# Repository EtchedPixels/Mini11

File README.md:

# Mini11: A Small 68HC11A System

The Mini11 is a small board that is designed to provide a complete large
68HC11 environment with a fairly low chip count. It provides 16K of ROM and
512K of RAM as well as breaking out all the spare I/O including the serial
and SPI in useful ways.

To keep cost down it's designed to use the many old 68HC11A series parts
that can be found in junk boxes and old boards. This has a different pinout
to the later processor variants.

## Requirements

- 68HC11A series processor (A0/A1/A8). 68HC811A probably works too
- 512K SRAM
- 27C256 or 28C256
- 74HC(T)139
- 74HC(T)00
- 74HC(T)573
- DS1233 reset controller
- 8MHz crystal
- pinheaders, sockets, resistors etc

## Construction

As the 68HC11 can be serial bootstrapped it is possible to assemble the
board and fit all the discrete parts and only the 68HC11 into its socket.
Fit jumpers JP1 and JP2 and apply power. You should be able to talk to the
board with db11 or similar tools.

If you have a part with ROM then you should also be able to boot from the
ROM if you boot with JP1 and JP2 removed. If the ROM contains Buffalo as
is usual then you will also need to jumper PE0 to ground. A 68HC11A8 with
Buffalo should then produce a boot message and you'll be able to talk to
the monitor.

The boot mode can also be used to check out the board after the other parts
are fitted. You can boot in single chip mode and then use db11 to turn off the
single chip mode and then check that the memory is behaving. Port A controls
the memory banking. Bit 3 turns the ROM on and off, bits 4-6 are the memory
bank.

With all the parts fitted you can burn firmware of choice into the ROM and
with the jumpers removed the chip should boot the firmware. Remember to use
the ".burn" file with the provided firmware or the tools to flip bit 0 and 2
as the board has D0 and D2 switched on the ROM

The provided firmware simply intializes the SD interface, loads the
first sector and runs it.

### Note

You cannot run an unmodified Buffalo from the ROM. It uses Port A pins for
tracing and this conflicts with the memory banking.

## ROM options

For a 27C256 you can load different firmware into each 16K bank and select
using JP3. For a 28C256 burn the firmware into the upper 16K and jumper JP3
to VCC.

## Rescuing Recalcitrant 68HC11A Parts

If you have problems with the 68HC11A such as it only coming up in bootstrap
mode then there are a few things to check.

### Wrong Config Byte

If the CONFIG byte is set to map in the internal ROM and the ROM contains
garbage or is absent (eg on a 68HC11A0/A1 part) then you can boot it into
single chip mode and use db11 to change the config byte to 0x0C or similar.

### Protected EEROM

The internal EEROM has protection options and some devices wih custom
firmware will set them. These can still be used as they will erase the
EEPROM when the serial boot is triggered. This will put 0F into the CONFIG
register so that will also then need reprogramming.

### Did You Remember D0/D2 Are Swapped In Your ROM Image

No.. opps

## External Interfaces

### J2: Serial (TTL Level)

Simple three wire interface with no flow control. Usually run at 9600 baud.

### J3: SPI (5v)

SPI. Provides the expected SPI interfaces as well as two chip select lines,
reset and the external IRQ (pulled up). Intended for an SD card and
optionally additional devices with an SPI mux/demux board. Remember to use
an SD adapter with voltage shifting.

### J4: Power

5v and ground, needs to be properly regulated. The board has an onboard
reset generator to handle power coming up gracefully.

## J5: GPIO

Three input ports mapped to port A bits 0-2

### J6: Analogue

Port E of the 68HC11.

## Jumpers

### JP1: MODA

Fit the jumper to set MODA low

### JP2: MODB

Fit the jumper to set MODB low

### JP3: ROM Select

Select bank on 27C256, set to 5V with a 28C256

## Software

At this point FUZIX. Build the "mini11" target, write the generated SD card
image raw to an SD card and boot the mini11 with it inserted. The console
runs at 9600 baud.

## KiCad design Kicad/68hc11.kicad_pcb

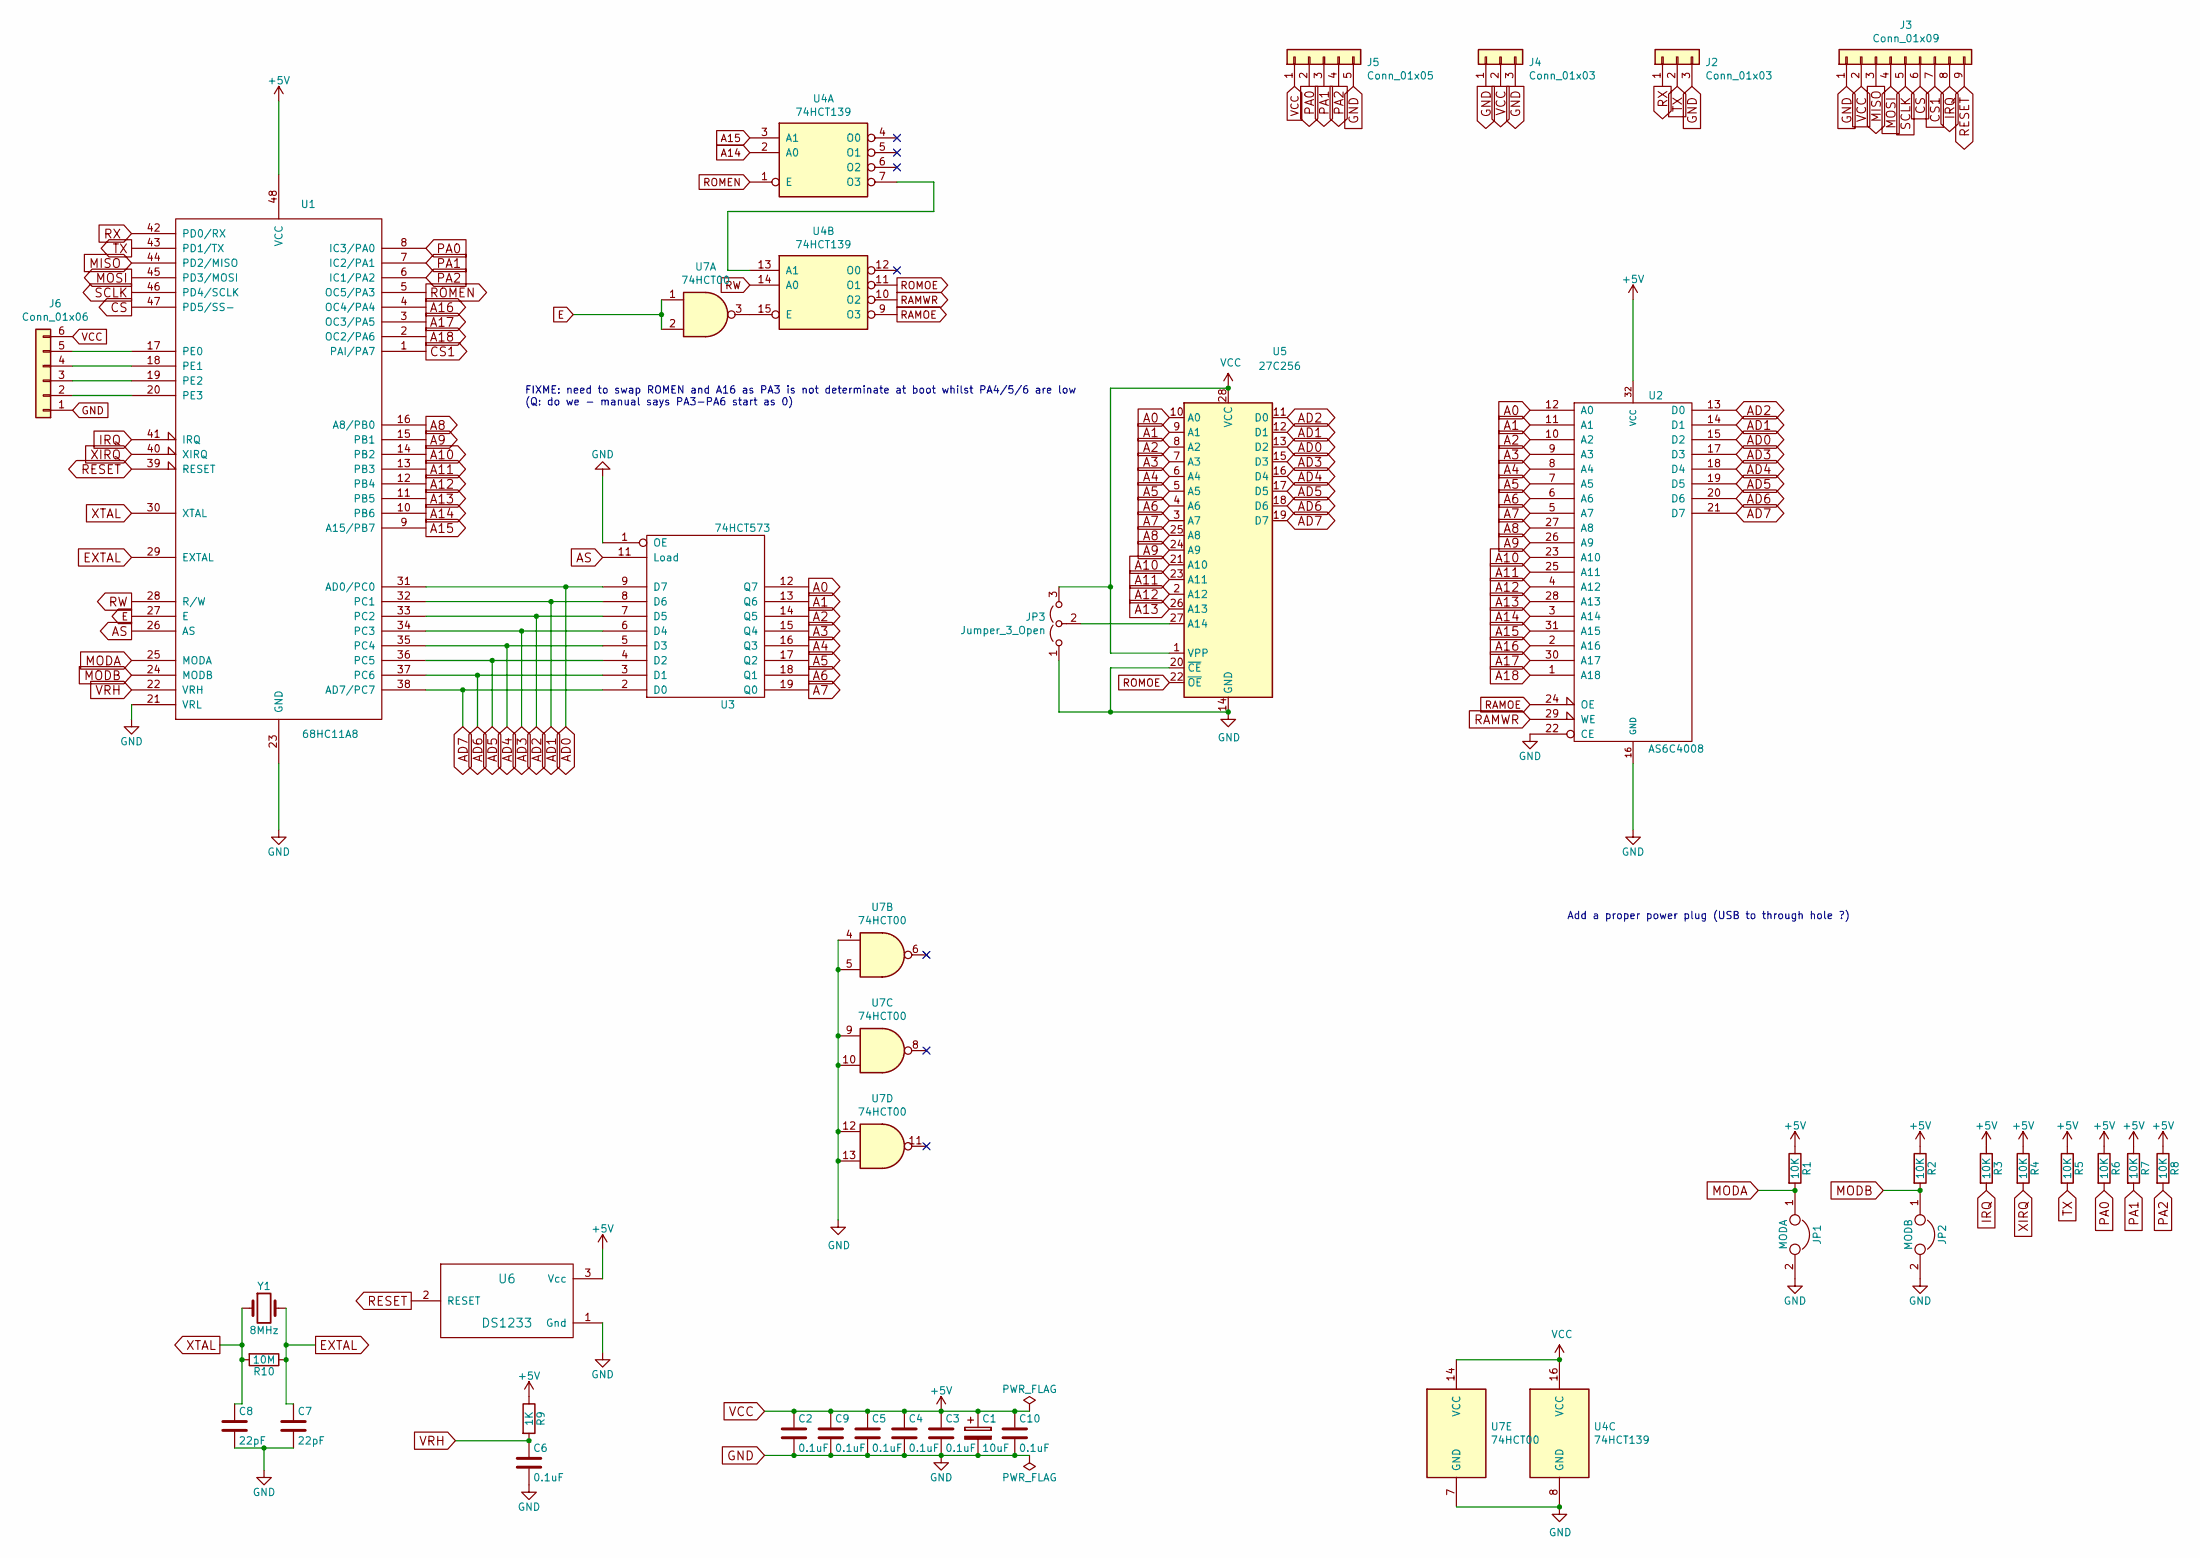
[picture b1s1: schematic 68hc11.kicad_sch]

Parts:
C1: 10uF; CP_Radial_D5.0mm_P2.00mm
C2, C3, C4, C5, C6, C10: 0.1uF; C_Disc_D3.0mm_W1.6mm_P2.50mm
C7, C8: 22pF; C_Disc_D3.0mm_W1.6mm_P2.50mm
C9: 0.1uF; C_Disc_D3.0mm_W2.0mm_P2.50mm
J2: Conn_01x03; PinHeader_1x03_P2.54mm_Horizontal
J3: Conn_01x09; PinHeader_1x09_P2.54mm_Vertical
J4: Conn_01x03; PinHeader_1x03_P2.54mm_Vertical
J5: Conn_01x05; PinHeader_1x05_P2.54mm_Vertical
J6: Conn_01x06; PinHeader_1x06_P2.54mm_Horizontal
JP1: MODA; PinHeader_1x02_P2.54mm_Vertical
JP2: MODB; PinHeader_1x02_P2.54mm_Vertical
JP3: Jumper_3_Open; PinHeader_1x03_P2.54mm_Vertical
R1, R2, R3, R4, R5, R6, R7, R8: 10K; R_Axial_DIN0207_L6.3mm_D2.5mm_P10.16mm_Horizontal
R9: 1K; R_Axial_DIN0207_L6.3mm_D2.5mm_P10.16mm_Horizontal
R10: 10M; R_Axial_DIN0207_L6.3mm_D2.5mm_P10.16mm_Horizontal
U1: 68HC11A8; DIP-48_W15.24mm
U2: AS6C4008; DIP-32_W15.24mm
U3: 74HCT573; DIP-20_W7.62mm
U4: 74HCT139; DIP-16_W7.62mm
U5: 27C256; DIP-28_W15.24mm
U6: DS1233; TO-92_Inline_Narrow_Oval
U7: 74HCT00; DIP-14_W7.62mm
Y1: 8MHz; Crystal_HC49-U_Vertical

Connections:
A0: U2.12 (A0), U3.12 (Q7), U5.10 (A0)
A1: U2.11 (A1), U3.13 (Q6), U5.9 (A1)
A2: U2.10 (A2), U3.14 (Q5), U5.8 (A2)
A3: U2.9 (A3), U3.15 (Q4), U5.7 (A3)
A4: U2.8 (A4), U3.16 (Q3), U5.6 (A4)
A5: U2.7 (A5), U3.17 (Q2), U5.5 (A5)
A6: U2.6 (A6), U3.18 (Q1), U5.4 (A6)
A7: U2.5 (A7), U3.19 (Q0), U5.3 (A7)
A8: U1.16 (A8/PB0), U2.27 (A8), U5.25 (A8)
A9: U1.15 (PB1), U2.26 (A9), U5.24 (A9)
A10: U1.14 (PB2), U2.23 (A10), U5.21 (A10)
A11: U1.13 (PB3), U2.25 (A11), U5.23 (A11)
A12: U1.12 (PB4), U2.4 (A12), U5.2 (A12)
A13: U1.11 (PB5), U2.28 (A13), U5.26 (A13)
A14: U1.10 (PB6), U2.3 (A14), U4.2 (A0)
A15: U1.9 (A15/PB7), U2.31 (A15), U4.3 (A1)
A16: U1.4 (OC4/PA4), U2.2 (A16)
A17: U1.3 (OC3/PA5), U2.30 (A17)
A18: U1.2 (OC2/PA6), U2.1 (A18)
AD0: U1.31 (AD0/PC0), U2.15 (D2), U3.9 (D7), U5.13 (D2)
AD1: U1.32 (PC1), U2.14 (D1), U3.8 (D6), U5.12 (D1)
AD2: U1.33 (PC2), U2.13 (D0), U3.7 (D5), U5.11 (D0)
AD3: U1.34 (PC3), U2.17 (D3), U3.6 (D4), U5.15 (D3)
AD4: U1.35 (PC4), U2.18 (D4), U3.5 (D3), U5.16 (D4)
AD5: U1.36 (PC5), U2.19 (D5), U3.4 (D2), U5.17 (D5)
AD6: U1.37 (PC6), U2.20 (D6), U3.3 (D1), U5.18 (D6)
AD7: U1.38 (AD7/PC7), U2.21 (D7), U3.2 (D0), U5.19 (D7)
AS: U1.26 (AS), U3.11 (Load)
CS: J3.6, U1.47 (PD5/SS-)
CS1: J3.7, U1.1 (PAI/PA7)
E: U1.27 (E), U7.1, U7.2
EXTAL: C7.1, R10.1, U1.29 (EXTAL), Y1.2
GND: C1.2, C2.2, C3.2, C4.2, C5.2, C6.2, C7.2, C8.2, C9.2, C10.2, J2.3, J3.1, J4.1, J4.3, J5.5, J6.1, JP1.2, JP2.2, JP3.1 (A), U1.21 (VRL), U1.23 (GND), U2.16 (GND), U2.22 (CE), U3.1 (OE), U3.10 (GND), U4.8 (GND), U5.14 (GND), U5.20 (~CE), U6.1 (Gnd), U7.4, U7.5, U7.7 (GND), U7.9, U7.10, U7.12, U7.13
IRQ: J3.8, R3.2, U1.41 (IRQ)
MISO: J3.3, U1.44 (PD2/MISO)
MODA: JP1.1, R1.2, U1.25 (MODA)
MODB: JP2.1, R2.2, U1.24 (MODB)
MOSI: J3.4, U1.45 (PD3/MOSI)
unnamed: J6.2, U1.20 (PE3)
unnamed: J6.3, U1.19 (PE2)
unnamed: J6.4, U1.18 (PE1)
unnamed: J6.5, U1.17 (PE0)
unnamed: JP3.2 (C), U5.27 (A14)
unnamed: U4.7 (O3), U4.13 (A1)
unnamed: U4.15 (E), U7.3
PA0: J5.2, R6.2, U1.8 (IC3/PA0)
PA1: J5.3, R7.2, U1.7 (IC2/PA1)
PA2: J5.4, R8.2, U1.6 (IC1/PA2)
RAMOE: U2.24 (OE), U4.9 (O3)
RAMWR: U2.29 (WE), U4.10 (O2)
RESET: J3.9, U1.39 (RESET), U6.2 (RESET)
ROMEN: U1.5 (OC5/PA3), U4.1 (E)
ROMOE: U4.11 (O1), U5.22 (~OE)
RW: U1.28 (R/W), U4.14 (A0)
RX: J2.1, U1.42 (PD0/RX)
SCLK: J3.5, U1.46 (PD4/SCLK)
TX: J2.2, R5.2, U1.43 (PD1/TX)
VCC: C1.1, C2.1, C3.1, C4.1, C5.1, C9.1, C10.1, J3.2, J4.2, J5.1, J6.6, JP3.3 (B), R1.1, R2.1, R3.1, R4.1, R5.1, R6.1, R7.1, R8.1, R9.1, U1.48 (VCC), U2.32 (VCC), U3.20 (VCC), U4.16 (VCC), U5.1 (VPP), U5.28 (VCC), U6.3 (Vcc), U7.14 (VCC)
VRH: C6.1, R9.2, U1.22 (VRH)
XIRQ: R4.2, U1.40 (XIRQ)
XTAL: C8.1, R10.2, U1.30 (XTAL), Y1.1

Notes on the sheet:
FIXME: need to swap ROMEN and A16 as PA3 is not determinate at boot whilst PA4/5/6 are low (Q: do we - manual says PA3-PA6 start as 0)
Add a proper power plug (USB to through hole ?)

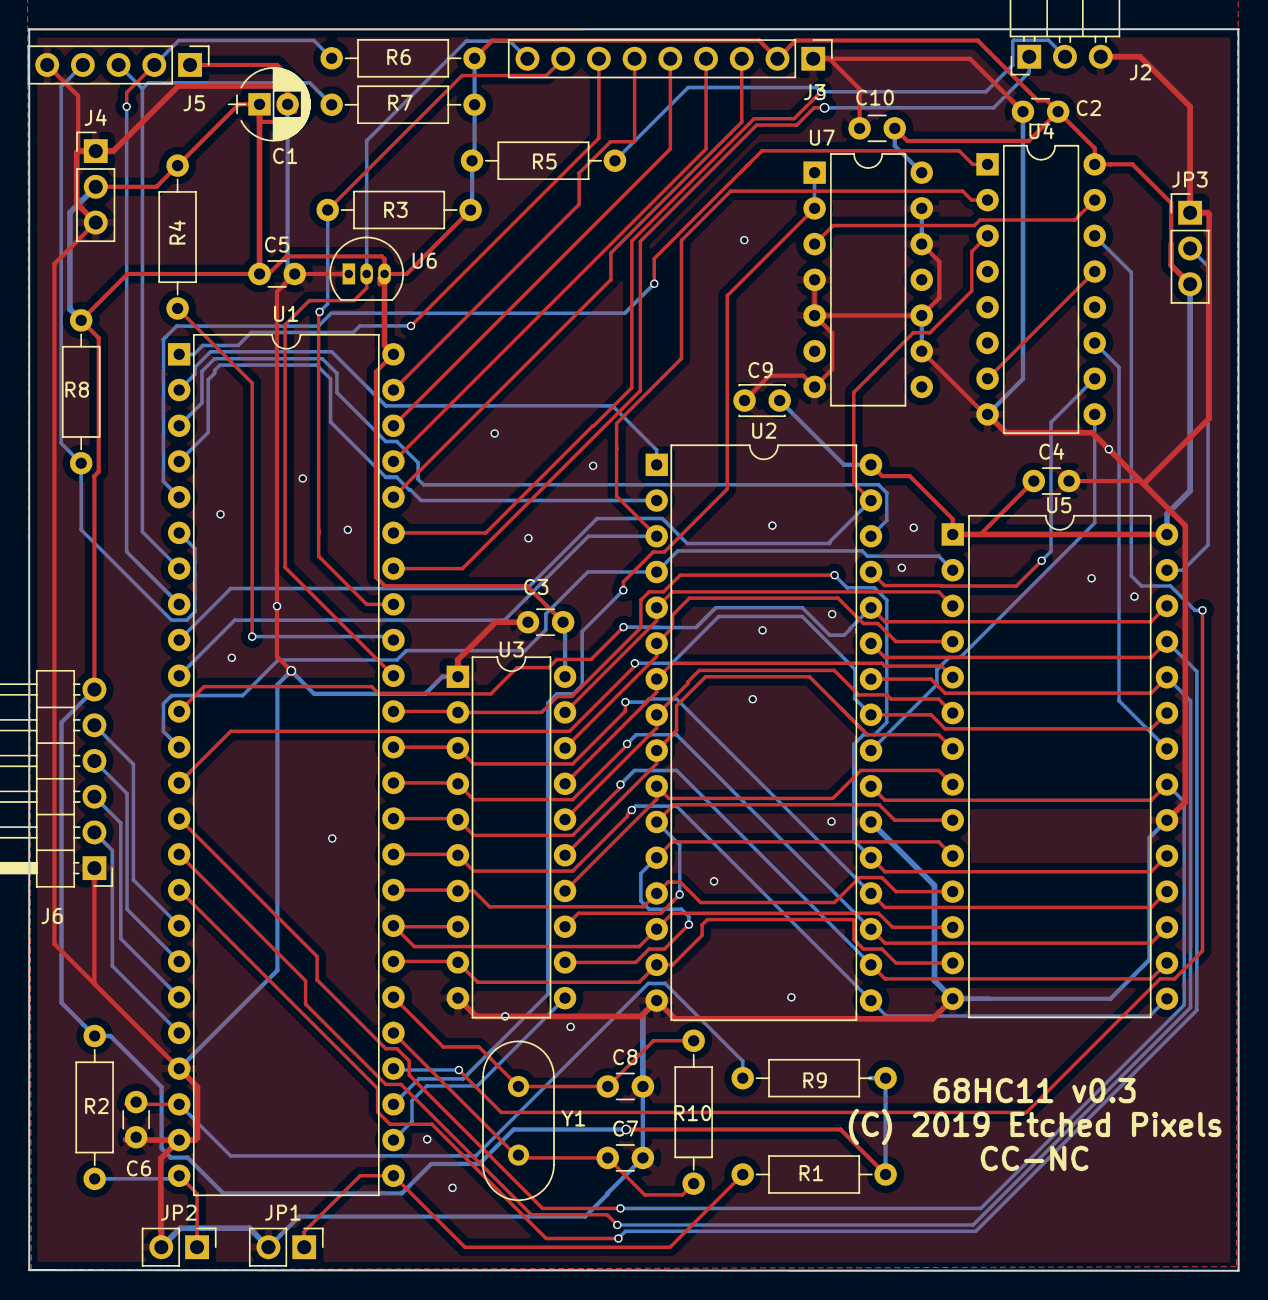
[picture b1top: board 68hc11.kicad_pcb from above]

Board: 2 copper layers, 86.0 x 88.3 mm, 36 parts (0 on the bottom side), 61 nets.

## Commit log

2023-03-05 Mini11: 68HC11A SBC
2023-03-06 firmware: update miniboot to the production one
2023-03-08 README: fix typo
2023-03-08 miniboot: set up PA7 at boot time
    Needed for the SPI mux/demux and the Wiznet 5500
2023-03-08 README: more typos

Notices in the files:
Kicad/68hc11.kicad_pcb:
(C) 2019 Etched Pixels
